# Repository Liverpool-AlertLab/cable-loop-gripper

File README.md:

This repository contains the design files required to manufacturee a cable loop gripper as well as the firmware and the code required to interface it with a ROS noetic system.

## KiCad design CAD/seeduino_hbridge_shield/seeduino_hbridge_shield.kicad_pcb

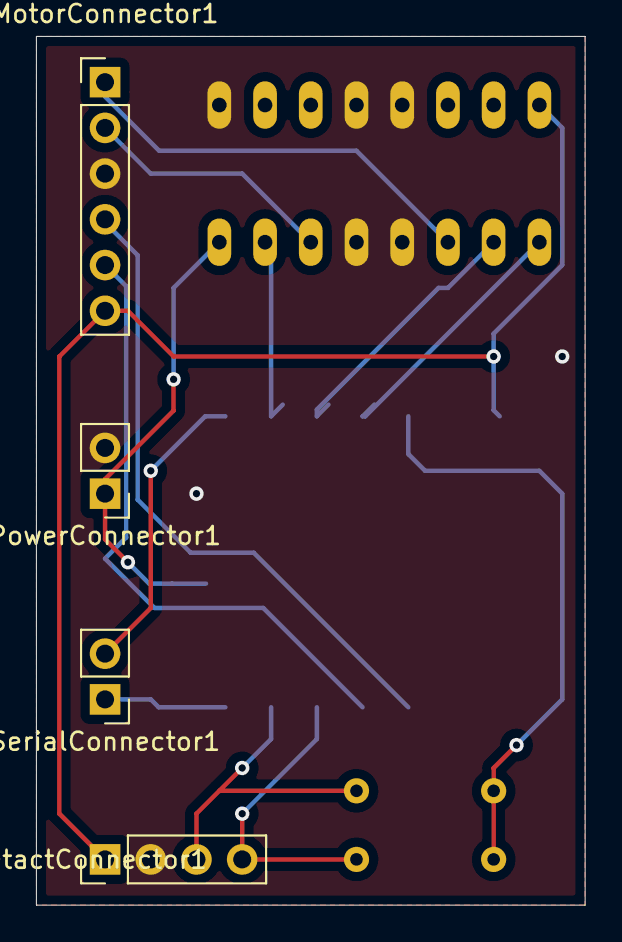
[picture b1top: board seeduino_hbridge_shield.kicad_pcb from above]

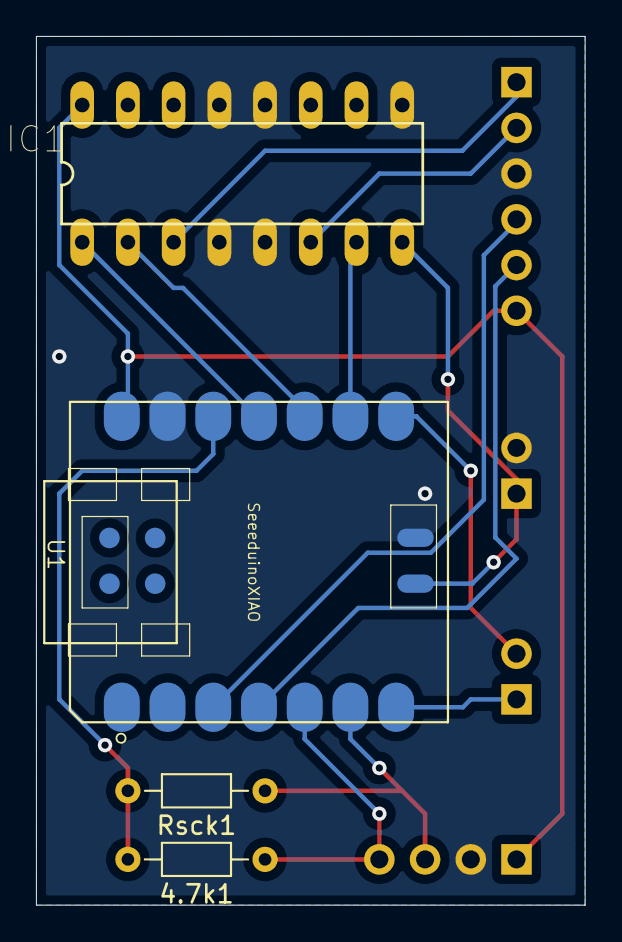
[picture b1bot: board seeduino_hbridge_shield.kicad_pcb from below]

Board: 2 copper layers, 30.5 x 48.3 mm, 8 parts (4 on the bottom side), 15 nets.

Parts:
4.7k1: Rsck; R_Axial_DIN0204_L3.6mm_D1.6mm_P7.62mm_Horizontal
IC1: SN754410; DIP16
MotorConnector1: Conn_01x06_Male; PinHeader_1x06_P2.54mm_Vertical
PowerConnector1: Conn_01x02_Male; PinHeader_1x02_P2.54mm_Vertical
Rsck1: 4.7k; R_Axial_DIN0204_L3.6mm_D1.6mm_P7.62mm_Horizontal
SerialConnector1: Conn_01x02_Male; PinHeader_1x02_P2.54mm_Vertical
SingletactConnector1: Conn_01x04_Male; PinHeader_1x04_P2.54mm_Vertical
U1: SeeeduinoXIAO; Seeeduino XIAO-MOUDLE14P-2.54-21X17.8MM

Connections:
3.3v: 4.7k1.2, Rsck1.2, U1.12
5V: IC1.16, MotorConnector1.6, SingletactConnector1.1, U1.14
6V: IC1.8, PowerConnector1.1, U1.15
EncoderA: MotorConnector1.4, U1.3
EncoderB: MotorConnector1.5, U1.4
GND: IC1.4, IC1.5, IC1.9, IC1.12, IC1.13, MotorConnector1.3, PowerConnector1.2, SingletactConnector1.2, U1.13, U1.16
MotorA: IC1.3, MotorConnector1.1
MotorAcontrol: IC1.2, U1.10
MotorB: IC1.6, MotorConnector1.2
MotorBcontrol: IC1.7, U1.9
PWM: IC1.1, U1.11
RX: SerialConnector1.2, U1.8
SCL: Rsck1.1, SingletactConnector1.3, U1.6
SDA: 4.7k1.1, SingletactConnector1.4, U1.5
TX: SerialConnector1.1, U1.7

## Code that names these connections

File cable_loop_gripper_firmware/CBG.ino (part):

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#include <AutoPID.h>
#include <Wire.h>

#define EncoderA    3
#define EncoderB    2
#define MotorA      10
#define MotorB      9
#define PWMMotor    8

#define BAUD        115200
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  void Brising_ISR();
  void Bfalling_ISR();

  attachInterrupt(digitalPinToInterrupt(EncoderA), Arising_ISR, RISING);
  attachInterrupt(digitalPinToInterrupt(EncoderA), Afalling_ISR, FALLING);
  attachInterrupt(digitalPinToInterrupt(EncoderB), Brising_ISR, RISING);
  attachInterrupt(digitalPinToInterrupt(EncoderB), Bfalling_ISR, FALLING);

  T0 = millis();
}
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
void initMotor()
{
  pinMode(MotorA, OUTPUT);
  pinMode(MotorB, OUTPUT);
  pinMode(PWMMotor, OUTPUT);

  digitalWrite(MotorA, LOW);
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
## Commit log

2024-03-21 Firs commit
2024-03-21 Added gitignore
2024-03-21 Added README
